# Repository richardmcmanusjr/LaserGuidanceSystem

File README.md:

# LaserGuidanceSystem
A simple laser guidance system using a quadrant photodiode and accompanying amplification circuitry to detect the position of incident light from a laser and orient itself toward the laser using two servo motors.

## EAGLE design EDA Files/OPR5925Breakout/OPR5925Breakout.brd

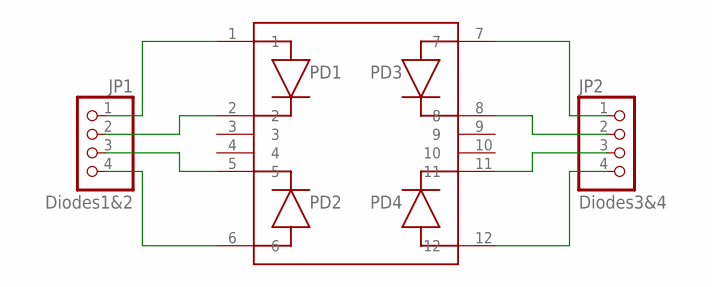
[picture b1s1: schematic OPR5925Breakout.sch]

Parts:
JP1: Diodes1&2; 1X04
JP2: Diodes3&4; 1X04
U$1: OPR5925

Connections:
unnamed: JP1.4, U$1.6
unnamed: JP1.3, U$1.5
unnamed: JP1.2, U$1.2
unnamed: JP1.1, U$1.1
unnamed: JP2.1, U$1.7
unnamed: JP2.2, U$1.8
unnamed: JP2.3, U$1.11
unnamed: JP2.4, U$1.12

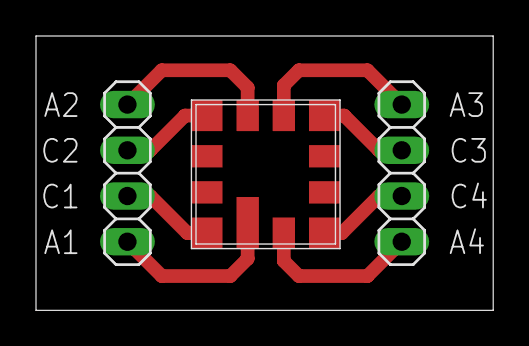
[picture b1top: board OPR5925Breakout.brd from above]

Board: 2 copper layers, 25.4 x 15.2 mm, 3 parts (0 on the bottom side), 8 nets.

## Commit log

2023-04-19 Added files via upload
2023-04-22 Added opr5925 class
2023-04-25 Added functionality to opr5925 class
2023-04-26 Fixed zero function
2023-04-26 Implemented get_x() and get_y()
2023-04-26 Fixed crosshair y_component
2023-04-26 Removed debugging Serial.print
2023-04-26 Added serial out for Processing GUI
2023-04-26 Fixed Processing GUI
2023-04-26 Fixed background
2023-04-26 Changed to manually drawn crosshairs
2023-04-26 Added flexibility for serial port selection
2023-04-28 Fixed OPR5925 Footprint
2023-04-30 Minor fixes
2023-05-01 Added via upload
2023-05-02 Organized folders
2023-05-02 Renamed files
2023-05-03 Fixed Overshot
2023-05-19 Updated DSP
